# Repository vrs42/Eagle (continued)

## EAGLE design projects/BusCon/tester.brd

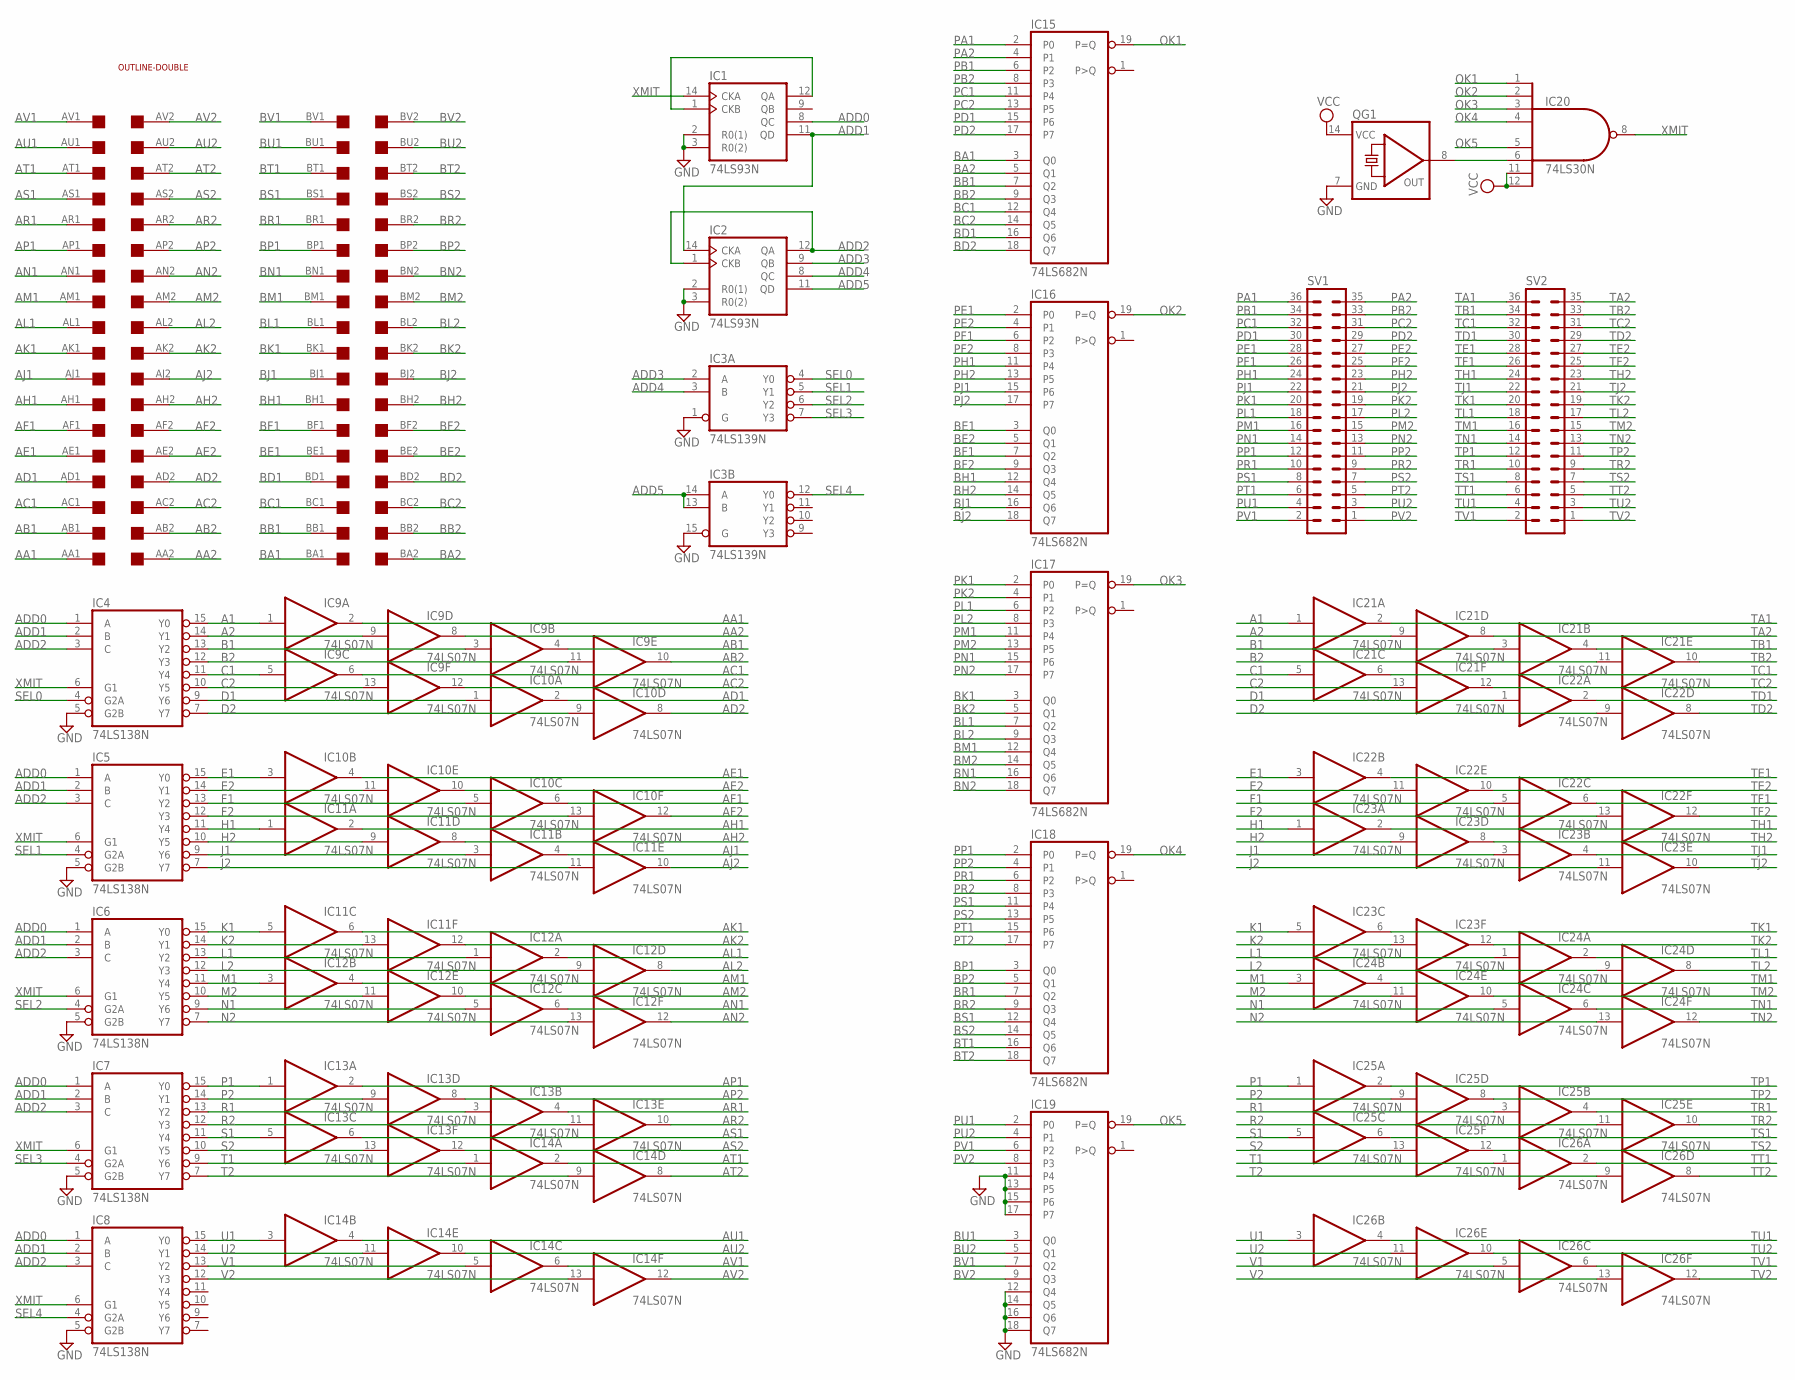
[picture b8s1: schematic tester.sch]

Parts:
IC1, IC2: 74LS93N; DIL14
IC3: 74LS139N; DIL16
IC4, IC5, IC6, IC7, IC8: 74LS138N; DIL16
IC9, IC10, IC11, IC12, IC13, IC14, IC21, IC22, IC23, IC24, IC25, IC26: 74LS07N; DIL14
IC15, IC16, IC17, IC18, IC19: 74LS682N; DIL20
IC20: 74LS30N; DIL14
QG1: QG5860; DIL14S
SV1, SV2: MA18-2
U$1: DOUBLE; EDGE-CON4
U$2: OUTLINE-DOUBLE; DOUBLE

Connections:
A1: IC4.15 (Y0), IC9.1 (I), IC21.1 (I)
A2: IC4.14 (Y1), IC9.9 (I), IC21.9 (I)
AA1: IC9.2 (O), U$1.AA1
AA2: IC9.8 (O), U$1.AA2
AB1: IC9.4 (O), U$1.AB1
AB2: IC9.10 (O), U$1.AB2
AC1: IC9.6 (O), U$1.AC1
AC2: IC9.12 (O), U$1.AC2
AD1: IC10.2 (O), U$1.AD1
AD2: IC10.8 (O), U$1.AD2
ADD0: IC1.8 (QC), IC4.1 (A), IC5.1 (A), IC6.1 (A), IC7.1 (A), IC8.1 (A)
ADD1: IC1.11 (QD), IC2.14 (CKA), IC4.2 (B), IC5.2 (B), IC6.2 (B), IC7.2 (B), IC8.2 (B)
ADD2: IC2.1 (CKB), IC2.12 (QA), IC4.3 (C), IC5.3 (C), IC6.3 (C), IC7.3 (C), IC8.3 (C)
ADD3: IC2.9 (QB), IC3.2 (A)
ADD4: IC2.8 (QC), IC3.3 (B)
ADD5: IC2.11 (QD), IC3.13 (B), IC3.14 (A)
AE1: IC10.4 (O), U$1.AE1
AE2: IC10.10 (O), U$1.AE2
AF1: IC10.6 (O), U$1.AF1
AF2: IC10.12 (O), U$1.AF2
AH1: IC11.2 (O), U$1.AH1
AH2: IC11.8 (O), U$1.AH2
AJ1: IC11.4 (O), U$1.AJ1
AJ2: IC11.10 (O), U$1.AJ2
AK1: IC11.6 (O), U$1.AK1
AK2: IC11.12 (O), U$1.AK2
AL1: IC12.2 (O), U$1.AL1
AL2: IC12.8 (O), U$1.AL2
AM1: IC12.4 (O), U$1.AM1
AM2: IC12.10 (O), U$1.AM2
AN1: IC12.6 (O), U$1.AN1
AN2: IC12.12 (O), U$1.AN2
AP1: IC13.2 (O), U$1.AP1
AP2: IC13.8 (O), U$1.AP2
AR1: IC13.4 (O), U$1.AR1
AR2: IC13.10 (O), U$1.AR2
AS1: IC13.6 (O), U$1.AS1
AS2: IC13.12 (O), U$1.AS2
AT1: IC14.2 (O), U$1.AT1
AT2: IC14.8 (O), U$1.AT2
AU1: IC14.4 (O), U$1.AU1
AU2: IC14.10 (O), U$1.AU2
AV1: IC14.6 (O), U$1.AV1
AV2: IC14.12 (O), U$1.AV2
B1: IC4.13 (Y2), IC9.3 (I), IC21.3 (I)
B2: IC4.12 (Y3), IC9.11 (I), IC21.11 (I)
BA1: IC15.3 (Q0), U$1.BA1
BA2: IC15.5 (Q1), U$1.BA2
BB1: IC15.7 (Q2), U$1.BB1
BB2: IC15.9 (Q3), U$1.BB2
BC1: IC15.12 (Q4), U$1.BC1
BC2: IC15.14 (Q5), U$1.BC2
BD1: IC15.16 (Q6), U$1.BD1
BD2: IC15.18 (Q7), U$1.BD2
BE1: IC16.3 (Q0), U$1.BE1
BE2: IC16.5 (Q1), U$1.BE2
BF1: IC16.7 (Q2), U$1.BF1
BF2: IC16.9 (Q3), U$1.BF2
BH1: IC16.12 (Q4), U$1.BH1
BH2: IC16.14 (Q5), U$1.BH2
BJ1: IC16.16 (Q6), U$1.BJ1
BJ2: IC16.18 (Q7), U$1.BJ2
BK1: IC17.3 (Q0), U$1.BK1
BK2: IC17.5 (Q1), U$1.BK2
BL1: IC17.7 (Q2), U$1.BL1
BL2: IC17.9 (Q3), U$1.BL2
BM1: IC17.12 (Q4), U$1.BM1
BM2: IC17.14 (Q5), U$1.BM2
BN1: IC17.16 (Q6), U$1.BN1
BN2: IC17.18 (Q7), U$1.BN2
BP1: IC18.3 (Q0), U$1.BP1
BP2: IC18.5 (Q1), U$1.BP2
BR1: IC18.7 (Q2), U$1.BR1
BR2: IC18.9 (Q3), U$1.BR2
BS1: IC18.12 (Q4), U$1.BS1
BS2: IC18.14 (Q5), U$1.BS2
BT1: IC18.16 (Q6), U$1.BT1
BT2: IC18.18 (Q7), U$1.BT2
BU1: IC19.3 (Q0), U$1.BU1
BU2: IC19.5 (Q1), U$1.BU2
BV1: IC19.7 (Q2), U$1.BV1
BV2: IC19.9 (Q3), U$1.BV2
C1: IC4.11 (Y4), IC9.5 (I), IC21.5 (I)
C2: IC4.10 (Y5), IC9.13 (I), IC21.13 (I)
CLK1: IC1.1 (CKB), IC1.12 (QA)
D1: IC4.9 (Y6), IC10.1 (I), IC22.1 (I)
D2: IC4.7 (Y7), IC10.9 (I), IC22.9 (I)
E1: IC5.15 (Y0), IC10.3 (I), IC22.3 (I)
E2: IC5.14 (Y1), IC10.11 (I), IC22.11 (I)
F1: IC5.13 (Y2), IC10.5 (I), IC22.5 (I)
F2: IC5.12 (Y3), IC10.13 (I), IC22.13 (I)
GND: IC1.2 (R0(1)), IC1.3 (R0(2)), IC1.10 (GND), IC2.2 (R0(1)), IC2.3 (R0(2)), IC2.10 (GND), IC3.1 (G), IC3.8 (GND), IC3.15 (G), IC4.5 (G2B), IC4.8 (GND), IC5.5 (G2B), IC5.8 (GND), IC6.5 (G2B), IC6.8 (GND), IC7.5 (G2B), IC7.8 (GND), IC8.5 (G2B), IC8.8 (GND), IC9.7 (GND), IC10.7 (GND), IC11.7 (GND), IC12.7 (GND), IC13.7 (GND), IC14.7 (GND), IC15.10 (GND), IC16.10 (GND), IC17.10 (GND), IC18.10 (GND), IC19.10 (GND), IC19.11 (P4), IC19.12 (Q4), IC19.13 (P5), IC19.14 (Q5), IC19.15 (P6), IC19.16 (Q6), IC19.17 (P7), IC19.18 (Q7), IC20.7 (GND), IC21.7 (GND), IC22.7 (GND), IC23.7 (GND), IC24.7 (GND), IC25.7 (GND), IC26.7 (GND), QG1.7 (GND)
H1: IC5.11 (Y4), IC11.1 (I), IC23.1 (I)
H2: IC5.10 (Y5), IC11.9 (I), IC23.9 (I)
J1: IC5.9 (Y6), IC11.3 (I), IC23.3 (I)
J2: IC5.7 (Y7), IC11.11 (I), IC23.11 (I)
K1: IC6.15 (Y0), IC11.5 (I), IC23.5 (I)
K2: IC6.14 (Y1), IC11.13 (I), IC23.13 (I)
L1: IC6.13 (Y2), IC12.1 (I), IC24.1 (I)
L2: IC6.12 (Y3), IC12.9 (I), IC24.9 (I)
M1: IC6.11 (Y4), IC12.3 (I), IC24.3 (I)
M2: IC6.10 (Y5), IC12.11 (I), IC24.11 (I)
N1: IC6.9 (Y6), IC12.5 (I), IC24.5 (I)
N2: IC6.7 (Y7), IC12.13 (I), IC24.13 (I)
unnamed: IC20.6 (I5), QG1.8 (OUT)
OK1: IC15.19 (P=Q), IC20.1 (I0)
OK2: IC16.19 (P=Q), IC20.2 (I1)
OK3: IC17.19 (P=Q), IC20.3 (I2)
OK4: IC18.19 (P=Q), IC20.4 (I3)
OK5: IC19.19 (P=Q), IC20.5 (I4)
P1: IC7.15 (Y0), IC13.1 (I), IC25.1 (I)
P2: IC7.14 (Y1), IC13.9 (I), IC25.9 (I)
PA1: IC15.2 (P0), SV1.36
PA2: IC15.4 (P1), SV1.35
PB1: IC15.6 (P2), SV1.34
PB2: IC15.8 (P3), SV1.33
PC1: IC15.11 (P4), SV1.32
PC2: IC15.13 (P5), SV1.31
PD1: IC15.15 (P6), SV1.30
PD2: IC15.17 (P7), SV1.29
PE1: IC16.2 (P0), SV1.28
PE2: IC16.4 (P1), SV1.27
PF1: IC16.6 (P2), SV1.26
PF2: IC16.8 (P3), SV1.25
PH1: IC16.11 (P4), SV1.24
PH2: IC16.13 (P5), SV1.23
PJ1: IC16.15 (P6), SV1.22
PJ2: IC16.17 (P7), SV1.21
PK1: IC17.2 (P0), SV1.20
PK2: IC17.4 (P1), SV1.19
PL1: IC17.6 (P2), SV1.18
PL2: IC17.8 (P3), SV1.17
PM1: IC17.11 (P4), SV1.16
PM2: IC17.13 (P5), SV1.15
PN1: IC17.15 (P6), SV1.14
PN2: IC17.17 (P7), SV1.13
PP1: IC18.2 (P0), SV1.12
PP2: IC18.4 (P1), SV1.11
PR1: IC18.6 (P2), SV1.10
PR2: IC18.8 (P3), SV1.9
PS1: IC18.11 (P4), SV1.8
PS2: IC18.13 (P5), SV1.7
PT1: IC18.15 (P6), SV1.6
PT2: IC18.17 (P7), SV1.5
PU1: IC19.2 (P0), SV1.4
PU2: IC19.4 (P1), SV1.3
PV1: IC19.6 (P2), SV1.2
PV2: IC19.8 (P3), SV1.1
R1: IC7.13 (Y2), IC13.3 (I), IC25.3 (I)
R2: IC7.12 (Y3), IC13.11 (I), IC25.11 (I)
S1: IC7.11 (Y4), IC13.5 (I), IC25.5 (I)
S2: IC7.10 (Y5), IC13.13 (I), IC25.13 (I)
SEL0: IC3.4 (Y0), IC4.4 (G2A)
SEL1: IC3.5 (Y1), IC5.4 (G2A)
SEL2: IC3.6 (Y2), IC6.4 (G2A)
SEL3: IC3.7 (Y3), IC7.4 (G2A)
SEL4: IC3.12 (Y0), IC8.4 (G2A)
T1: IC7.9 (Y6), IC14.1 (I), IC26.1 (I)
T2: IC7.7 (Y7), IC14.9 (I), IC26.9 (I)
TA1: IC21.2 (O), SV2.36
TA2: IC21.8 (O), SV2.35
TB1: IC21.4 (O), SV2.34
TB2: IC21.10 (O), SV2.33
TC1: IC21.6 (O), SV2.32
TC2: IC21.12 (O), SV2.31
TD1: IC22.2 (O), SV2.30
TD2: IC22.8 (O), SV2.29
TE1: IC22.4 (O), SV2.28
TE2: IC22.10 (O), SV2.27
TF1: IC22.6 (O), SV2.26
TF2: IC22.12 (O), SV2.25
TH1: IC23.2 (O), SV2.24
TH2: IC23.8 (O), SV2.23
TJ1: IC23.4 (O), SV2.22
TJ2: IC23.10 (O), SV2.21
TK1: IC23.6 (O), SV2.20
TK2: IC23.12 (O), SV2.19
TL1: IC24.2 (O), SV2.18
TL2: IC24.8 (O), SV2.17
TM1: IC24.4 (O), SV2.16
TM2: IC24.10 (O), SV2.15
TN1: IC24.6 (O), SV2.14
TN2: IC24.12 (O), SV2.13
TP1: IC25.2 (O), SV2.12
TP2: IC25.8 (O), SV2.11
TR1: IC25.4 (O), SV2.10
TR2: IC25.10 (O), SV2.9
TS1: IC25.6 (O), SV2.8
TS2: IC25.12 (O), SV2.7
TT1: IC26.2 (O), SV2.6
TT2: IC26.8 (O), SV2.5
TU1: IC26.4 (O), SV2.4
TU2: IC26.10 (O), SV2.3
TV1: IC26.6 (O), SV2.2
TV2: IC26.12 (O), SV2.1
U1: IC8.15 (Y0), IC14.3 (I), IC26.3 (I)
U2: IC8.14 (Y1), IC14.11 (I), IC26.11 (I)
V1: IC8.13 (Y2), IC14.5 (I), IC26.5 (I)
V2: IC8.12 (Y3), IC14.13 (I), IC26.13 (I)
VCC: IC1.5 (VCC), IC2.5 (VCC), IC3.16 (VCC), IC4.16 (VCC), IC5.16 (VCC), IC6.16 (VCC), IC7.16 (VCC), IC8.16 (VCC), IC9.14 (VCC), IC10.14 (VCC), IC11.14 (VCC), IC12.14 (VCC), IC13.14 (VCC), IC14.14 (VCC), IC15.20 (VCC), IC16.20 (VCC), IC17.20 (VCC), IC18.20 (VCC), IC19.20 (VCC), IC20.11 (I6), IC20.12 (I7), IC20.14 (VCC), IC21.14 (VCC), IC22.14 (VCC), IC23.14 (VCC), IC24.14 (VCC), IC25.14 (VCC), IC26.14 (VCC), QG1.14 (VCC)
XMIT: IC1.14 (CKA), IC4.6 (G1), IC5.6 (G1), IC6.6 (G1), IC7.6 (G1), IC8.6 (G1), IC20.8 (O)

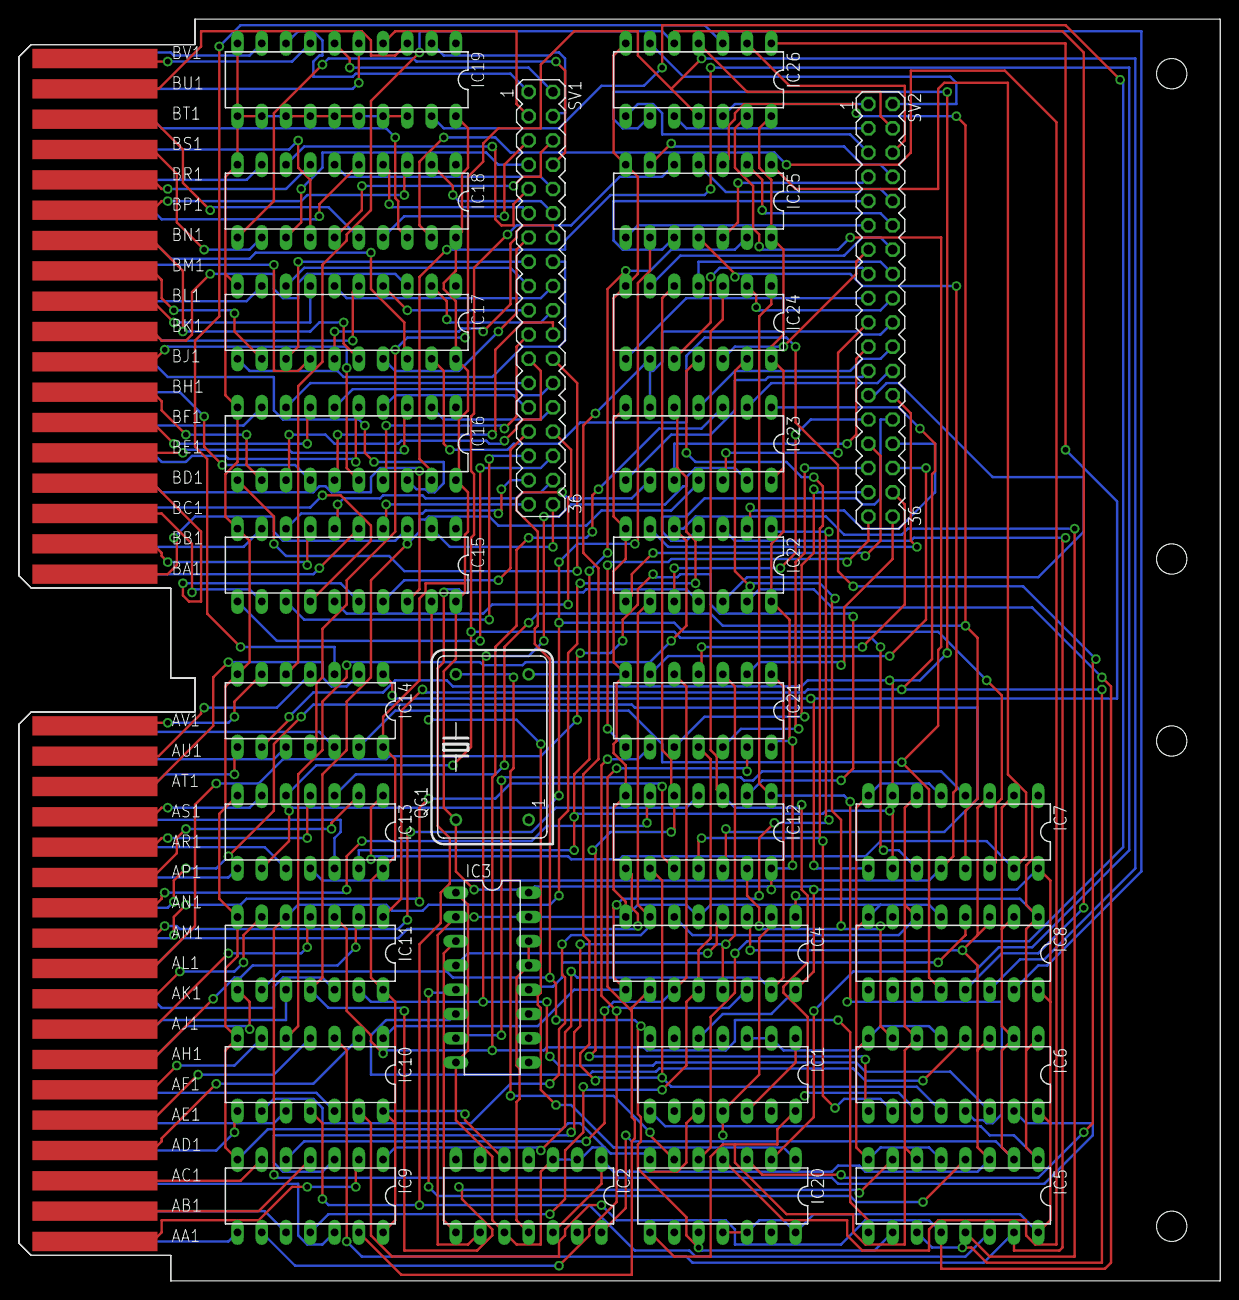
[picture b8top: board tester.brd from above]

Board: 2 copper layers, 125.7 x 132.1 mm, 31 parts (0 on the bottom side), 201 nets.
